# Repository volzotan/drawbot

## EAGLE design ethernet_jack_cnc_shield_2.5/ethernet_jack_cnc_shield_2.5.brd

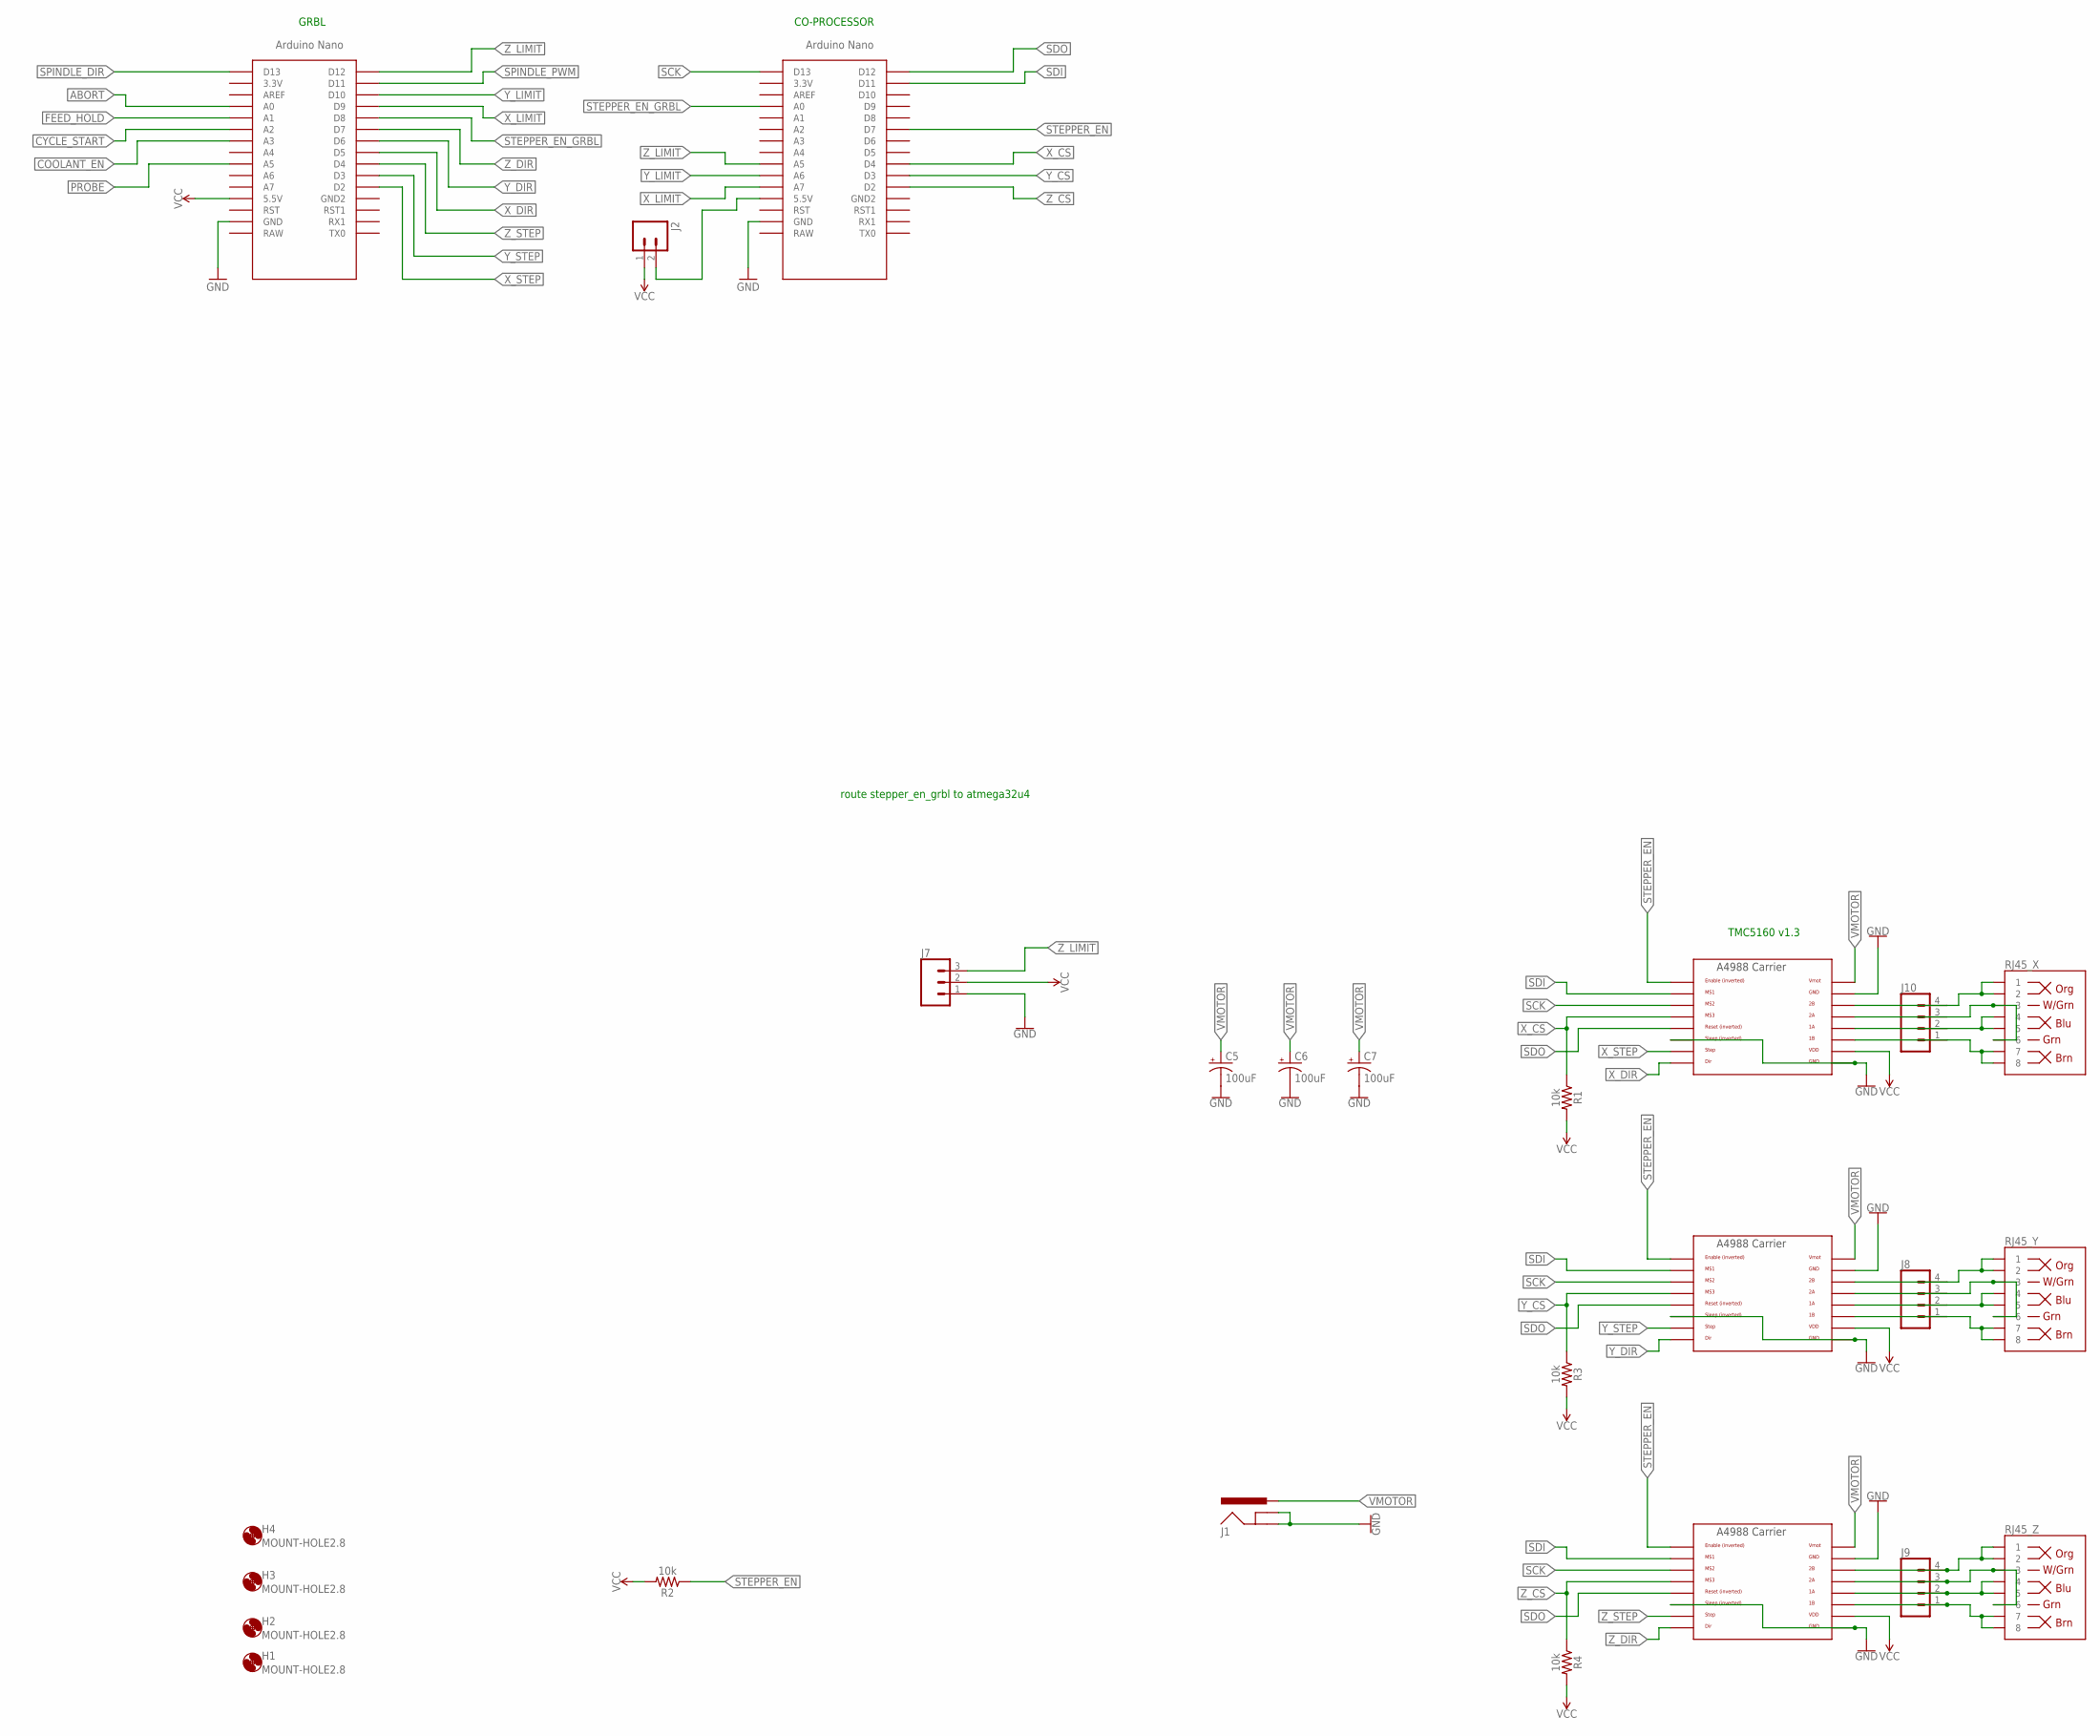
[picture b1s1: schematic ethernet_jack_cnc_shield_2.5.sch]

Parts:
C5, C6, C7: 100uF; PANASONIC_D
H1, H2, H3, H4: MOUNT-HOLE2.8; 2,8
J1: POWER_JACKPTH_BREAD; POWER_JACK_PTH_BREAD
J2: M02PTH; 1X02
J7: CONN_03; 1X03
J8, J9, J10: CONN_04; 1X04
R1, R2, R3, R4: 10k; 1206
RJ45_X, RJ45_Y, RJ45_Z: RJ45; RJ45-8
U$2, U$3, U$4: A4988BREAKOUT
U$5, U$7: NANO

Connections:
ABORT: U$5.A0
COOLANT_EN: U$5.A3
CYCLE_START: U$5.A2
FEED_HOLD: U$5.A1
GND: C5.-, C6.-, C7.-, J1.GND, J1.GNDBREAK, J7.1, U$2.GND, U$2.GND@0 (GND), U$2.SLP (SLEEP), U$3.GND, U$3.GND@0 (GND), U$3.SLP (SLEEP), U$4.GND, U$4.GND@0 (GND), U$4.SLP (SLEEP), U$5.GND, U$7.GND
unnamed: J10.4, RJ45_X.1, RJ45_X.2, U$4.2B
unnamed: J2.2, U$7.5V (5.5V)
unnamed: J10.3, RJ45_X.3, RJ45_X.6, U$4.2A
unnamed: J10.2, RJ45_X.4, RJ45_X.5, U$4.1A
unnamed: J10.1, RJ45_X.7, RJ45_X.8, U$4.1B
unnamed: J8.4, RJ45_Y.1, RJ45_Y.2, U$2.2B
unnamed: J8.3, RJ45_Y.3, RJ45_Y.6, U$2.2A
unnamed: J8.2, RJ45_Y.4, RJ45_Y.5, U$2.1A
unnamed: J8.1, RJ45_Y.7, RJ45_Y.8, U$2.1B
unnamed: J9.4, RJ45_Z.1, RJ45_Z.2, U$3.2B
unnamed: J9.3, RJ45_Z.3, RJ45_Z.6, U$3.2A
unnamed: J9.2, RJ45_Z.4, RJ45_Z.5, U$3.1A
unnamed: J9.1, RJ45_Z.7, RJ45_Z.8, U$3.1B
PROBE: U$5.A5
SCK: U$2.MS2, U$3.MS2, U$4.MS2, U$7.D13
SDI: U$2.MS1, U$3.MS1, U$4.MS1, U$7.D11
SDO: U$2.RST, U$3.RST, U$4.RST, U$7.D12
SPINDLE_DIR: U$5.D13
SPINDLE_PWM: U$5.D11
STEPPER_EN: R2.1, U$2.EN, U$3.EN, U$4.EN, U$7.D7
STEPPER_EN_GRBL: U$5.D8, U$7.A0
VCC: J2.1, J7.2, R1.2, R2.2, R3.2, R4.2, U$2.VDD, U$3.VDD, U$4.VDD, U$5.5V (5.5V)
VMOTOR: C5.+, C6.+, C7.+, J1.PWR, U$2.VMOT, U$3.VMOT, U$4.VMOT
X_CS: R1.1, U$4.MS3, U$7.D4
X_DIR: U$4.DIR, U$5.D5
X_LIMIT: U$5.D9, U$7.A7
X_STEP: U$4.STEP, U$5.D2
Y_CS: R3.1, U$2.MS3, U$7.D3
Y_DIR: U$2.DIR, U$5.D6
Y_LIMIT: U$5.D10, U$7.A6
Y_STEP: U$2.STEP, U$5.D3
Z_CS: R4.1, U$3.MS3, U$7.D2
Z_DIR: U$3.DIR, U$5.D7
Z_LIMIT: J7.3, U$5.D12, U$7.A5
Z_STEP: U$3.STEP, U$5.D4

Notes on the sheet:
route stepper_en_grbl to atmega32u4
GRBL
CO-PROCESSOR
TMC5160 v1.3

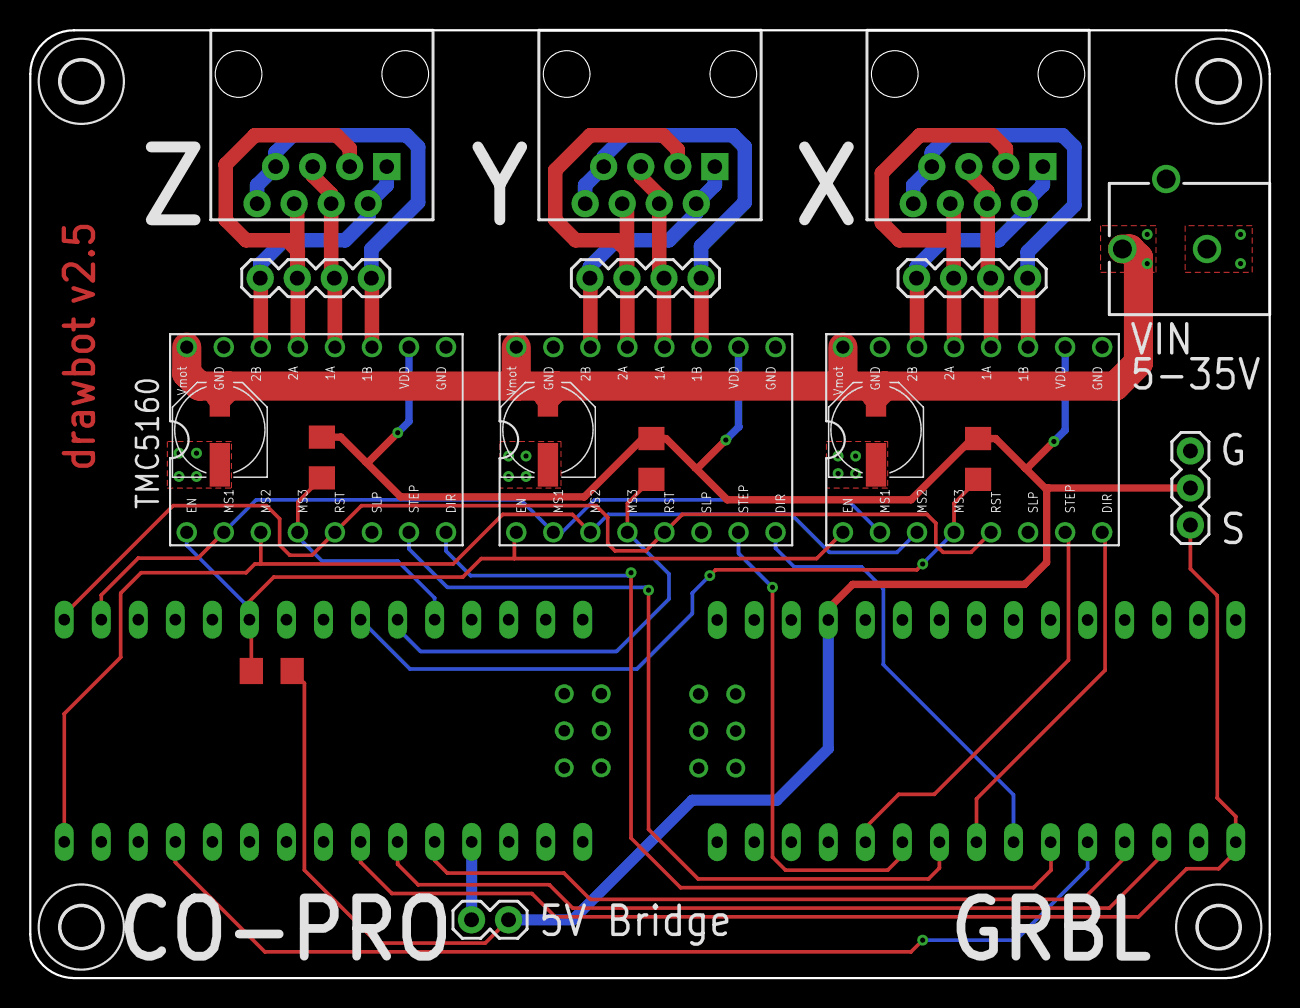
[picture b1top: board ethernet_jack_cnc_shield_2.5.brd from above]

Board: 2 copper layers, 85.0 x 65.0 mm, 25 parts (0 on the bottom side), 33 nets.

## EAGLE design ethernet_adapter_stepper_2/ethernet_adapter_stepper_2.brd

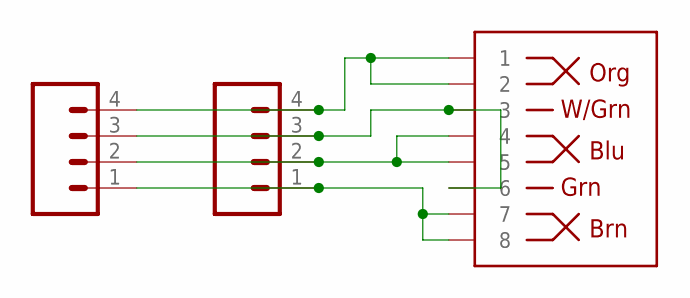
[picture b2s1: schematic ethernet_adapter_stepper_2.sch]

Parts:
J1: RJ45; RJ45-8
J2: CONN_04; 1X04
J4: CONN_04SCREW; SCREWTERMINAL-3.5MM-4

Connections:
unnamed: J1.1, J1.2, J2.4, J4.4
unnamed: J1.4, J1.5, J2.2, J4.2
unnamed: J1.3, J1.6, J2.3, J4.3
unnamed: J1.7, J1.8, J2.1, J4.1

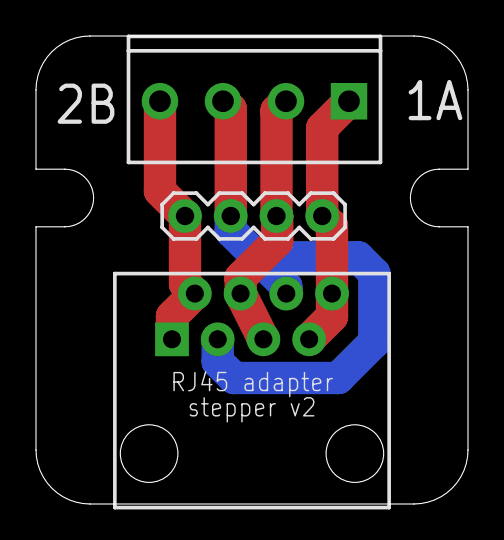
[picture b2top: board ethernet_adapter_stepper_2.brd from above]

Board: 2 copper layers, 24.0 x 26.0 mm, 3 parts (0 on the bottom side), 4 nets.

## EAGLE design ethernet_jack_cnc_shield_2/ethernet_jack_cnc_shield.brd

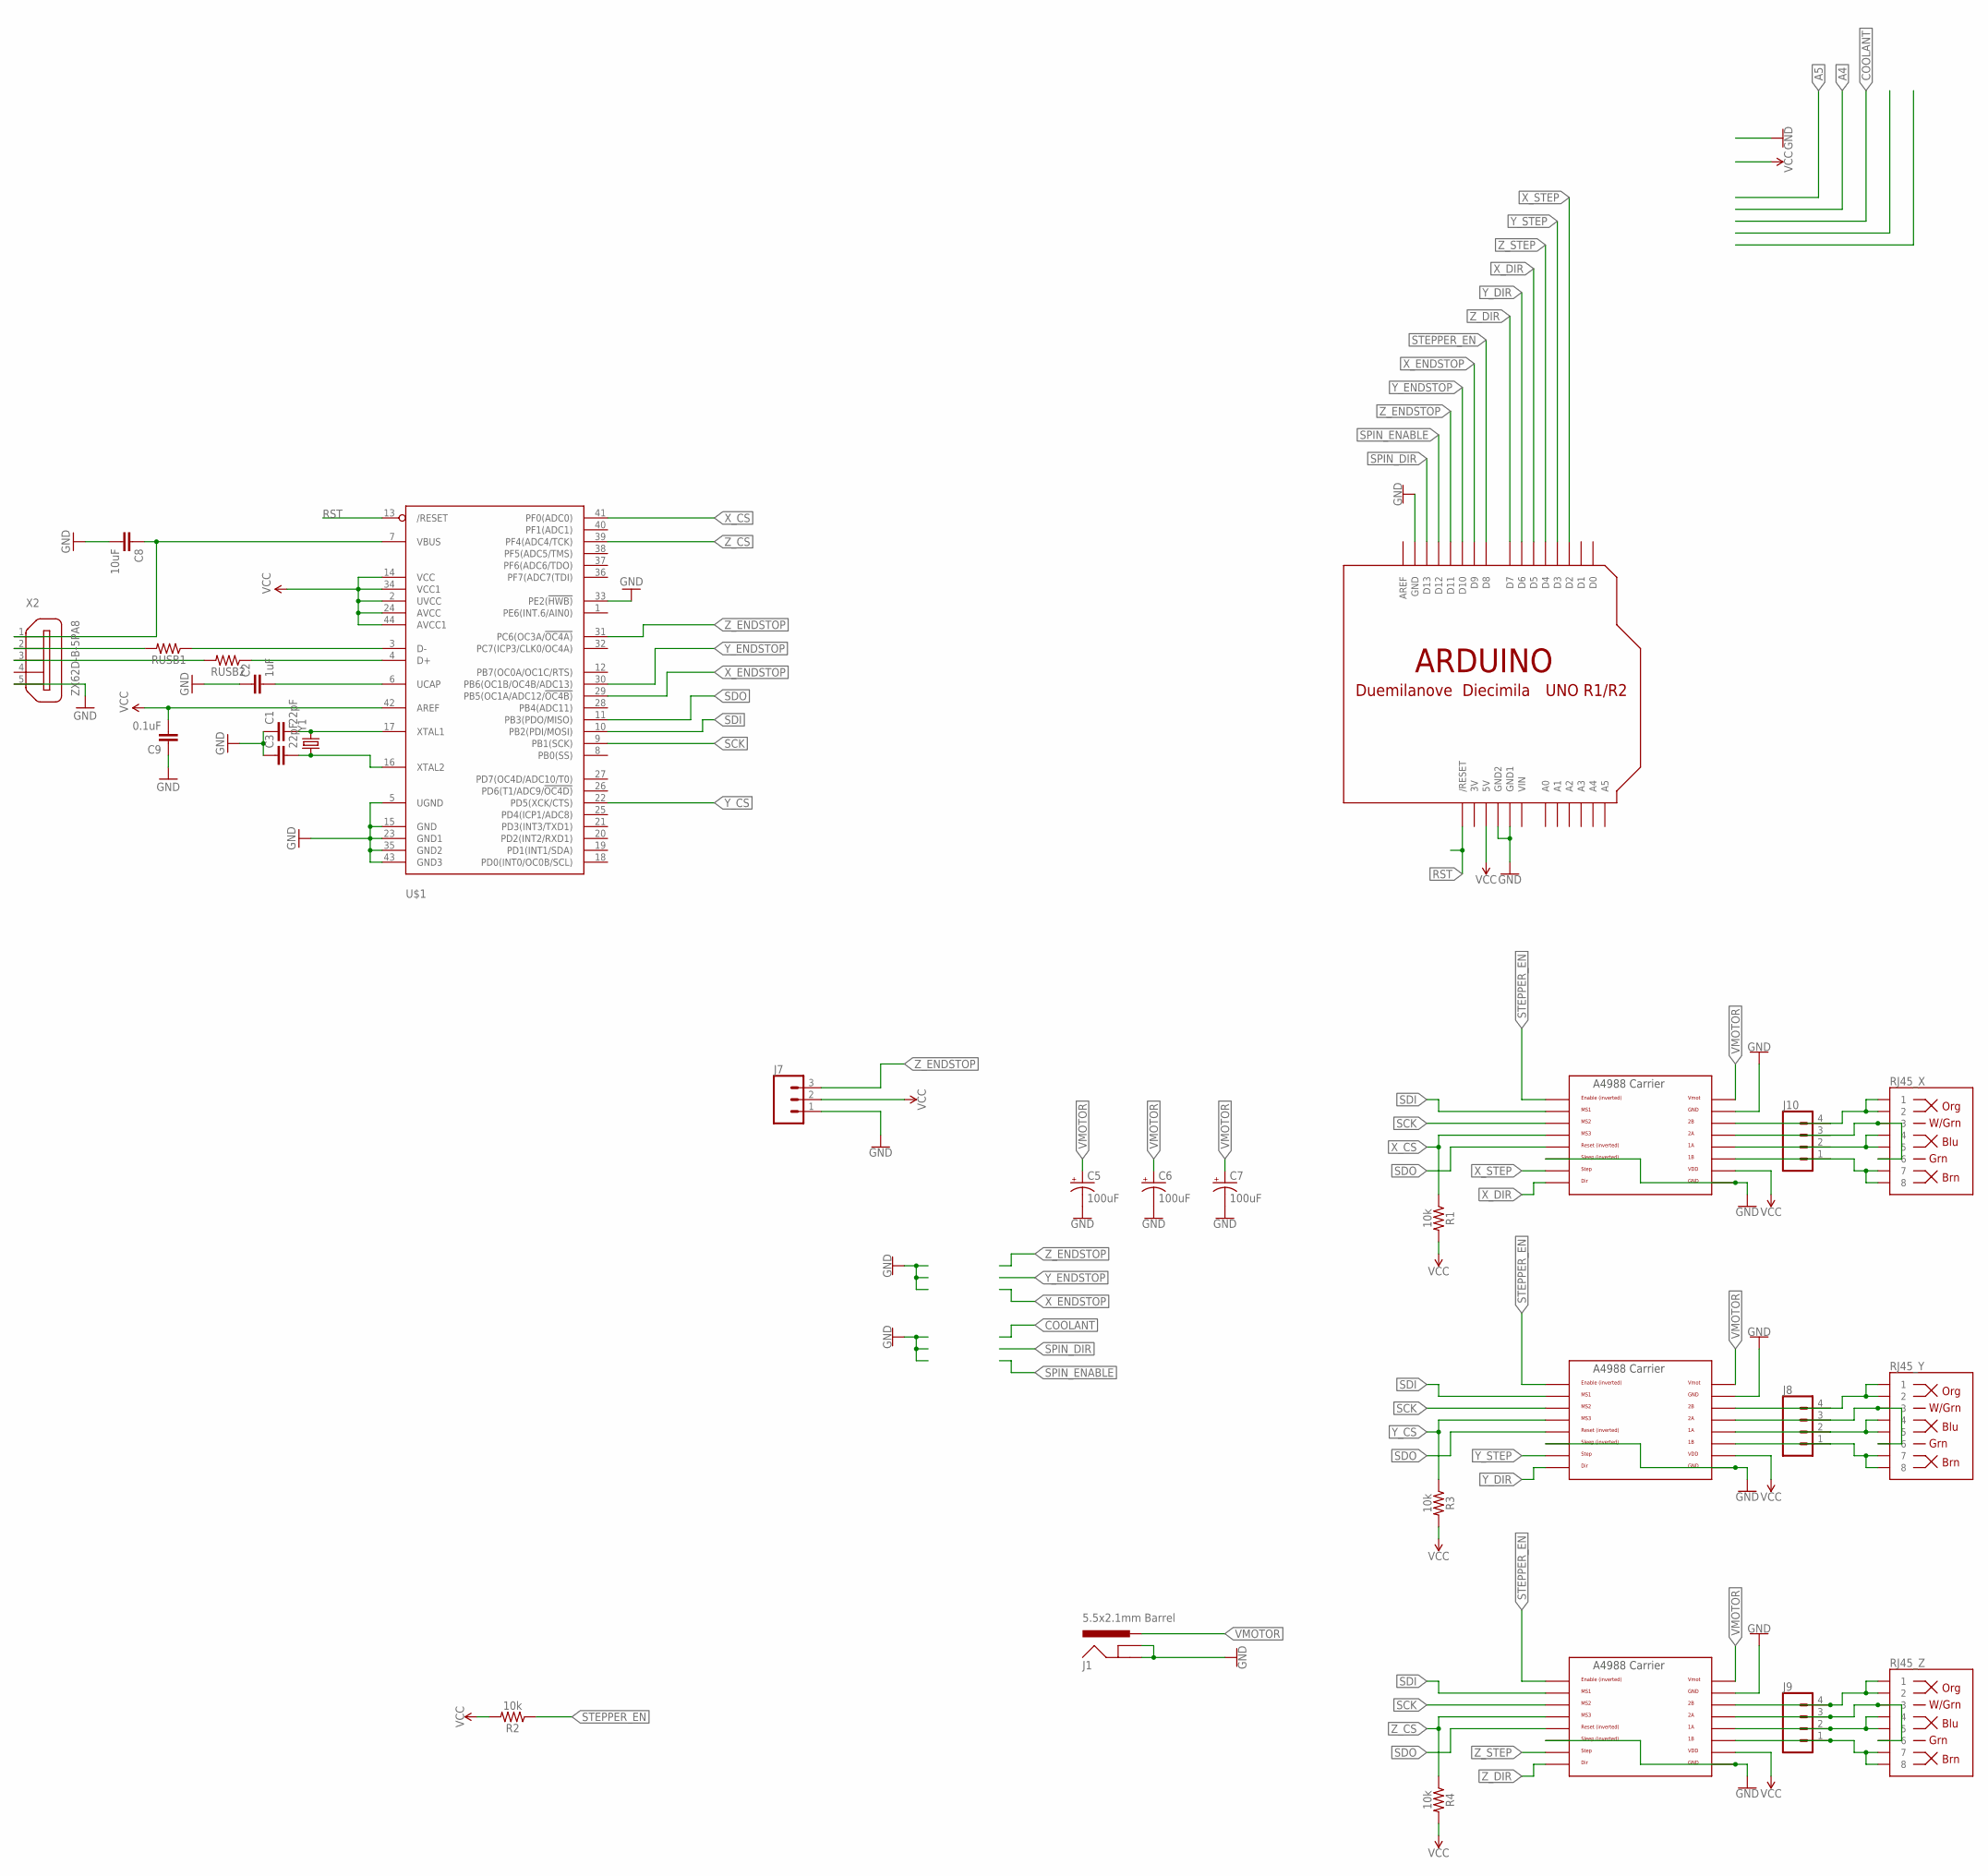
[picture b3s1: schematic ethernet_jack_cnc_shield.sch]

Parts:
C1, C3: 22pF; 1206
C2: 1uF; 1206
C5, C6, C7: 100uF; PANASONIC_D
C8: 10uF; 1206
C9: 0.1uF; 1206
J1: 5.5x2.1mm Barrel; POWER_JACK_SMD
J7: CONN_03; 1X03
J8, J9, J10: CONN_04; 1X04
R1, R2, R3, R4: 10k; 1206
RJ45_X, RJ45_Y, RJ45_Z: RJ45; RJ45-8
RUSB1, RUSB2: RESISTOR1206; 1206
U$1: ATMEGA32U4-AU; TQFP44
U$2, U$3, U$4: A4988BREAKOUT
U$6: ARDUINOUNO; ARDUINO
X2: ZX62D-B-5PA8
Y1: CRYSTALCRYSTAL-SMD-5X3-16MHZ; CRYSTAL-SMD-5X3

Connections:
3V: U$6.3V
GND: C1.1, C2.1, C3.1, C5.-, C6.-, C7.-, C8.2, C9.1, J1.GND (GNDBREAK), J1.P$4 (GND), J7.1, U$1.5 (UGND), U$1.15 (GND), U$1.23 (GND1), U$1.33 (PE2(!HWB)), U$1.35 (GND2), U$1.43 (GND3), U$2.GND, U$2.GND@0 (GND), U$2.SLP (SLEEP), U$3.GND, U$3.GND@0 (GND), U$3.SLP (SLEEP), U$4.GND, U$4.GND@0 (GND), U$4.SLP (SLEEP), U$6.GND, U$6.GND1, U$6.GND2, X2.5
unnamed: J10.4, RJ45_X.1, RJ45_X.2, U$4.2B
unnamed: RUSB1.1, U$1.3 (D-)
unnamed: J10.3, RJ45_X.3, RJ45_X.6, U$4.2A
unnamed: RUSB2.1, U$1.4 (D+)
unnamed: J10.2, RJ45_X.4, RJ45_X.5, U$4.1A
unnamed: C2.2, U$1.6 (UCAP)
unnamed: J10.1, RJ45_X.7, RJ45_X.8, U$4.1B
unnamed: C1.2, U$1.17 (XTAL1), Y1.3 (2)
unnamed: C3.2, U$1.16 (XTAL2), Y1.1
unnamed: RUSB1.2, X2.2
unnamed: RUSB2.2, X2.3
unnamed: J8.4, RJ45_Y.1, RJ45_Y.2, U$2.2B
unnamed: J8.3, RJ45_Y.3, RJ45_Y.6, U$2.2A
unnamed: J8.2, RJ45_Y.4, RJ45_Y.5, U$2.1A
unnamed: J8.1, RJ45_Y.7, RJ45_Y.8, U$2.1B
unnamed: J9.4, RJ45_Z.1, RJ45_Z.2, U$3.2B
unnamed: J9.3, RJ45_Z.3, RJ45_Z.6, U$3.2A
unnamed: J9.2, RJ45_Z.4, RJ45_Z.5, U$3.1A
unnamed: J9.1, RJ45_Z.7, RJ45_Z.8, U$3.1B
RST: U$1.13 (/RESET), U$6.RESET (/RESET)
SCK: U$1.9 (PB1(SCK)), U$2.MS2, U$3.MS2, U$4.MS2
SDI: U$1.10 (PB2(PDI/MOSI)), U$2.MS1, U$3.MS1, U$4.MS1
SDO: U$1.11 (PB3(PDO/MISO)), U$2.RST, U$3.RST, U$4.RST
SPIN_DIR: U$6.D13
SPIN_ENABLE: U$6.D12
STEPPER_EN: R2.1, U$2.EN, U$3.EN, U$4.EN, U$6.D8
VBUS: C8.1, U$1.7 (VBUS), X2.1
VCC: C9.2, J7.2, R1.2, R2.2, R3.2, R4.2, U$1.2 (UVCC), U$1.14 (VCC), U$1.24 (AVCC), U$1.34 (VCC1), U$1.42 (AREF), U$1.44 (AVCC1), U$2.VDD, U$3.VDD, U$4.VDD, U$6.5V
VIN: U$6.VIN
VMOTOR: C5.+, C6.+, C7.+, J1.VIN0 (PWR), U$2.VMOT, U$3.VMOT, U$4.VMOT
X_CS: R1.1, U$1.41 (PF0(ADC0)), U$4.MS3
X_DIR: U$4.DIR, U$6.D5
X_ENDSTOP: U$1.29 (PB5(OC1A/ADC12/!OC4B)), U$6.D9
X_STEP: U$4.STEP, U$6.D2
Y_CS: R3.1, U$1.22 (PD5(XCK/CTS)), U$2.MS3
Y_DIR: U$2.DIR, U$6.D6
Y_ENDSTOP: U$1.30 (PB6(OC1B/OC4B/ADC13)), U$6.D10
Y_STEP: U$2.STEP, U$6.D3
Z_CS: R4.1, U$1.39 (PF4(ADC4/TCK)), U$3.MS3
Z_DIR: U$3.DIR, U$6.D7
Z_ENDSTOP: J7.3, U$1.31 (PC6(OC3A/!OC4A)), U$6.D11
Z_STEP: U$3.STEP, U$6.D4

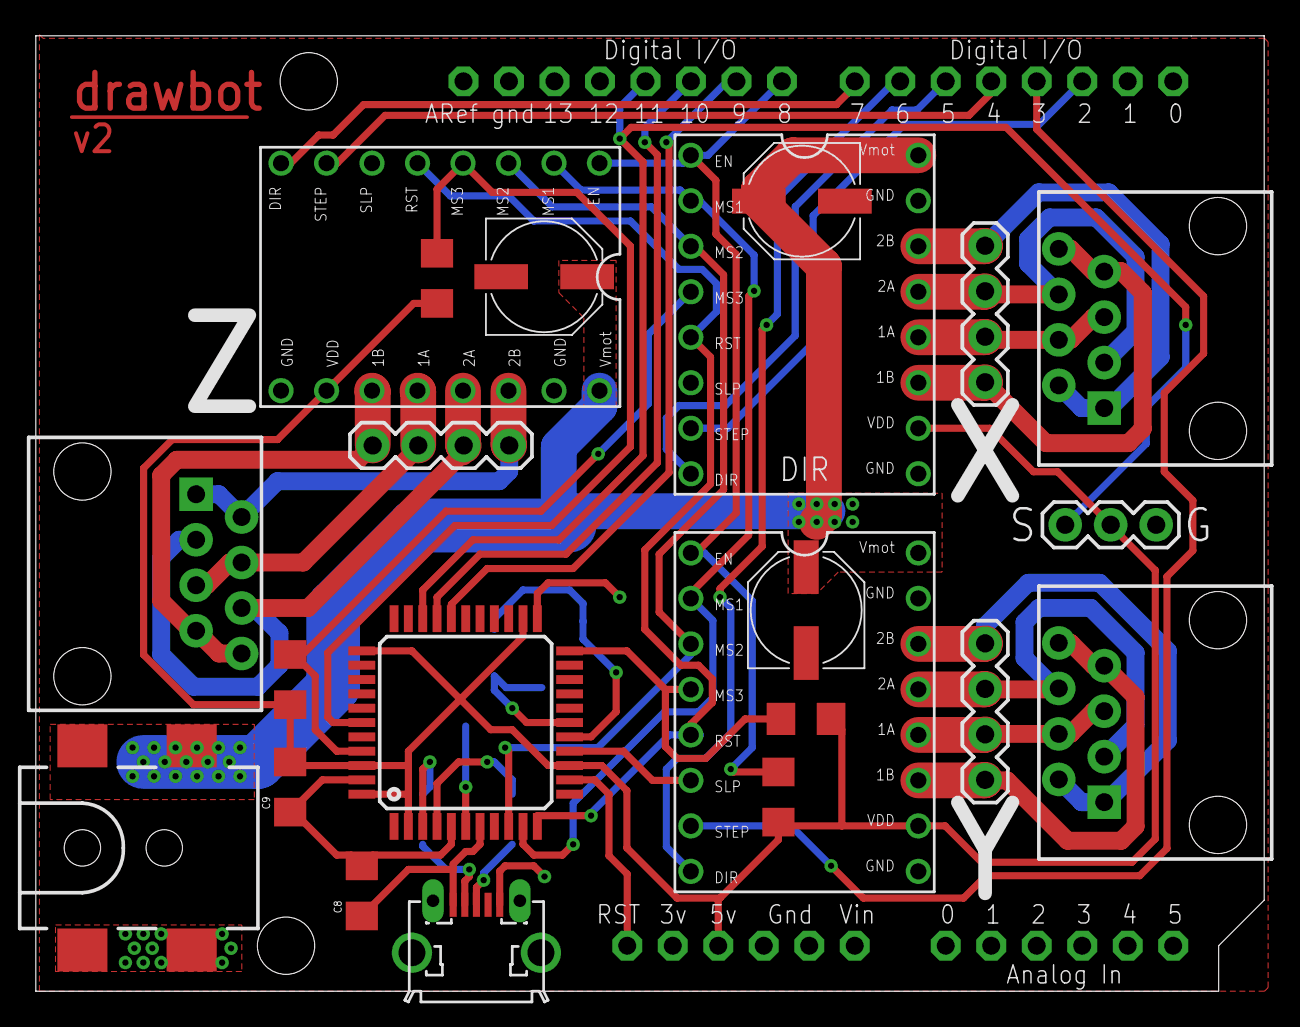
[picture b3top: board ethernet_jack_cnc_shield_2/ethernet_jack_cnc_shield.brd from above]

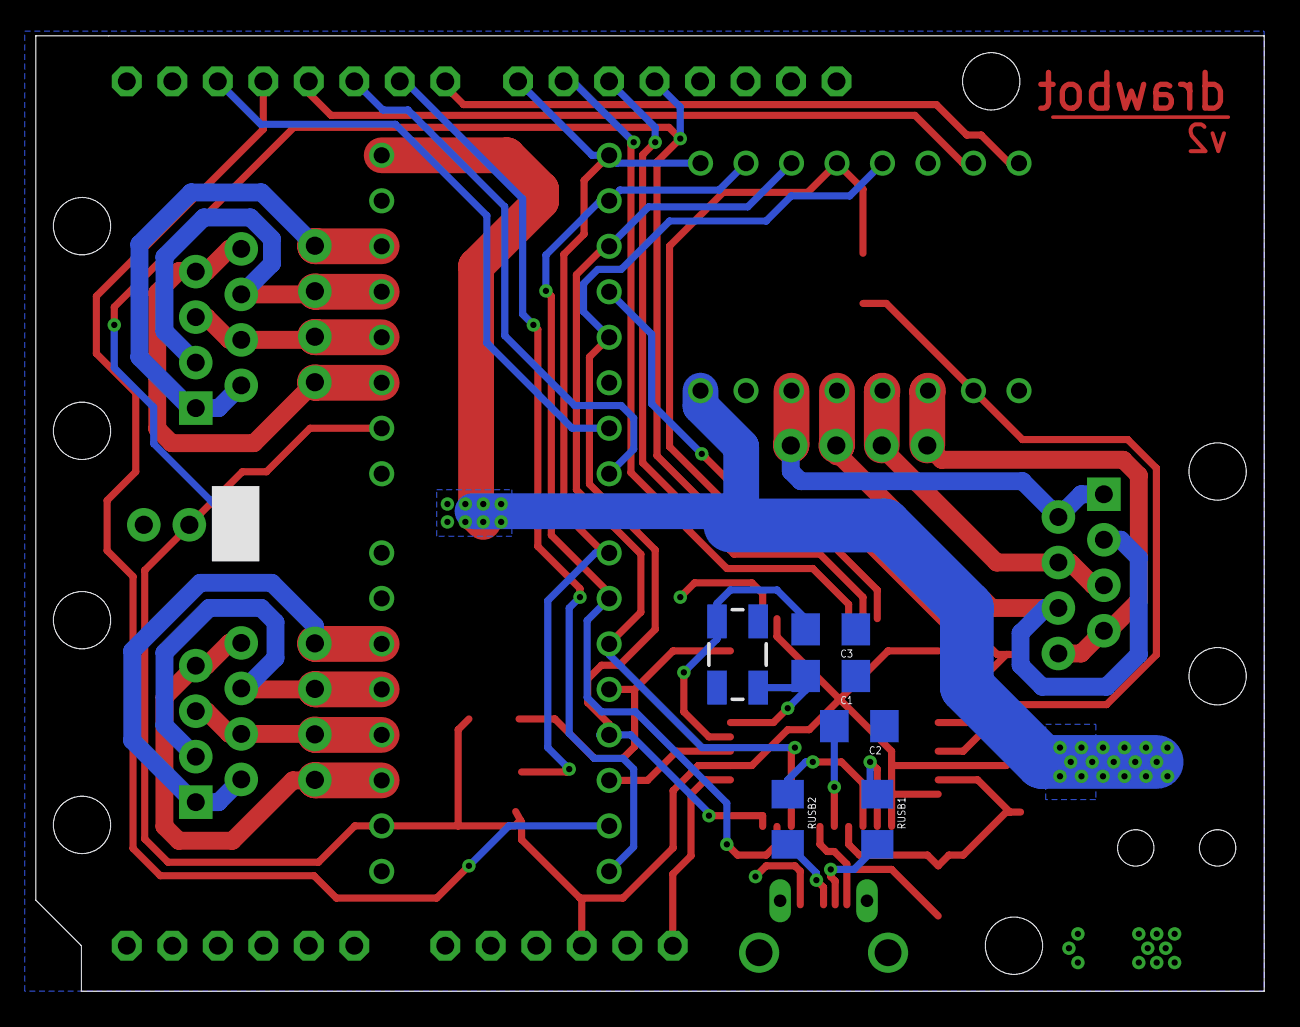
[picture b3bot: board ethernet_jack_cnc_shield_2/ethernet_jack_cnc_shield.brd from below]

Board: 2 copper layers, 68.6 x 53.3 mm, 29 parts (6 on the bottom side), 40 nets.

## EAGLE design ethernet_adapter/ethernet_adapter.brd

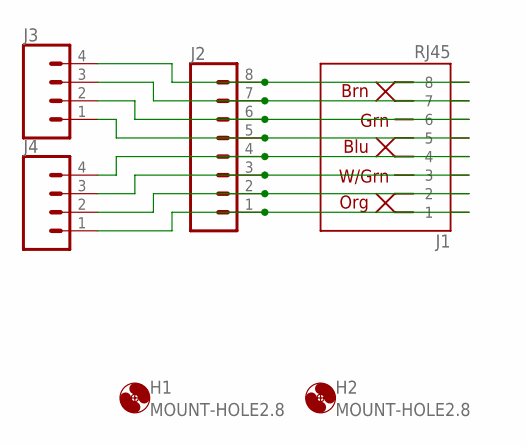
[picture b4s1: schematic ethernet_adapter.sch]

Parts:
H1, H2: MOUNT-HOLE2.8; 2,8
J1: RJ45; RJ45-8
J2: CONN_08LONGPADS; 1X08_LONGPADS
J3, J4: CONN_04SCREW; SCREWTERMINAL-3.5MM-4

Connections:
unnamed: J1.8, J2.8, J3.4
unnamed: J1.7, J2.7, J3.3
unnamed: J1.6, J2.6, J3.2
unnamed: J1.5, J2.5, J3.1
unnamed: J1.4, J2.4, J4.4
unnamed: J1.3, J2.3, J4.3
unnamed: J1.2, J2.2, J4.2
unnamed: J1.1, J2.1, J4.1

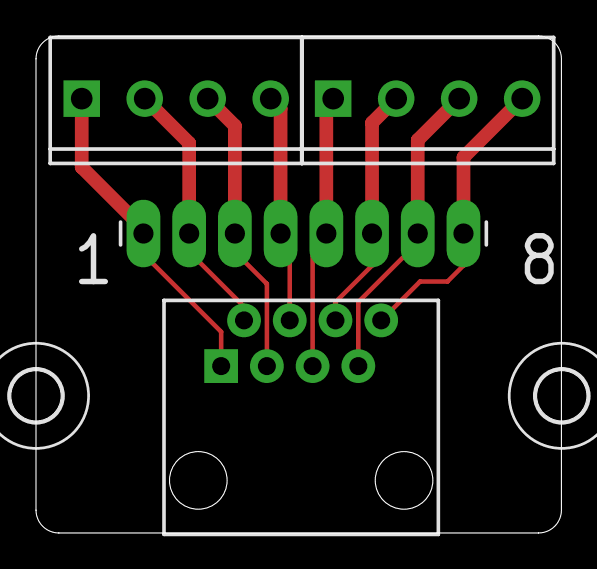
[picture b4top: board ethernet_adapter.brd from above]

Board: 2 copper layers, 29.2 x 27.6 mm, 6 parts (0 on the bottom side), 8 nets.

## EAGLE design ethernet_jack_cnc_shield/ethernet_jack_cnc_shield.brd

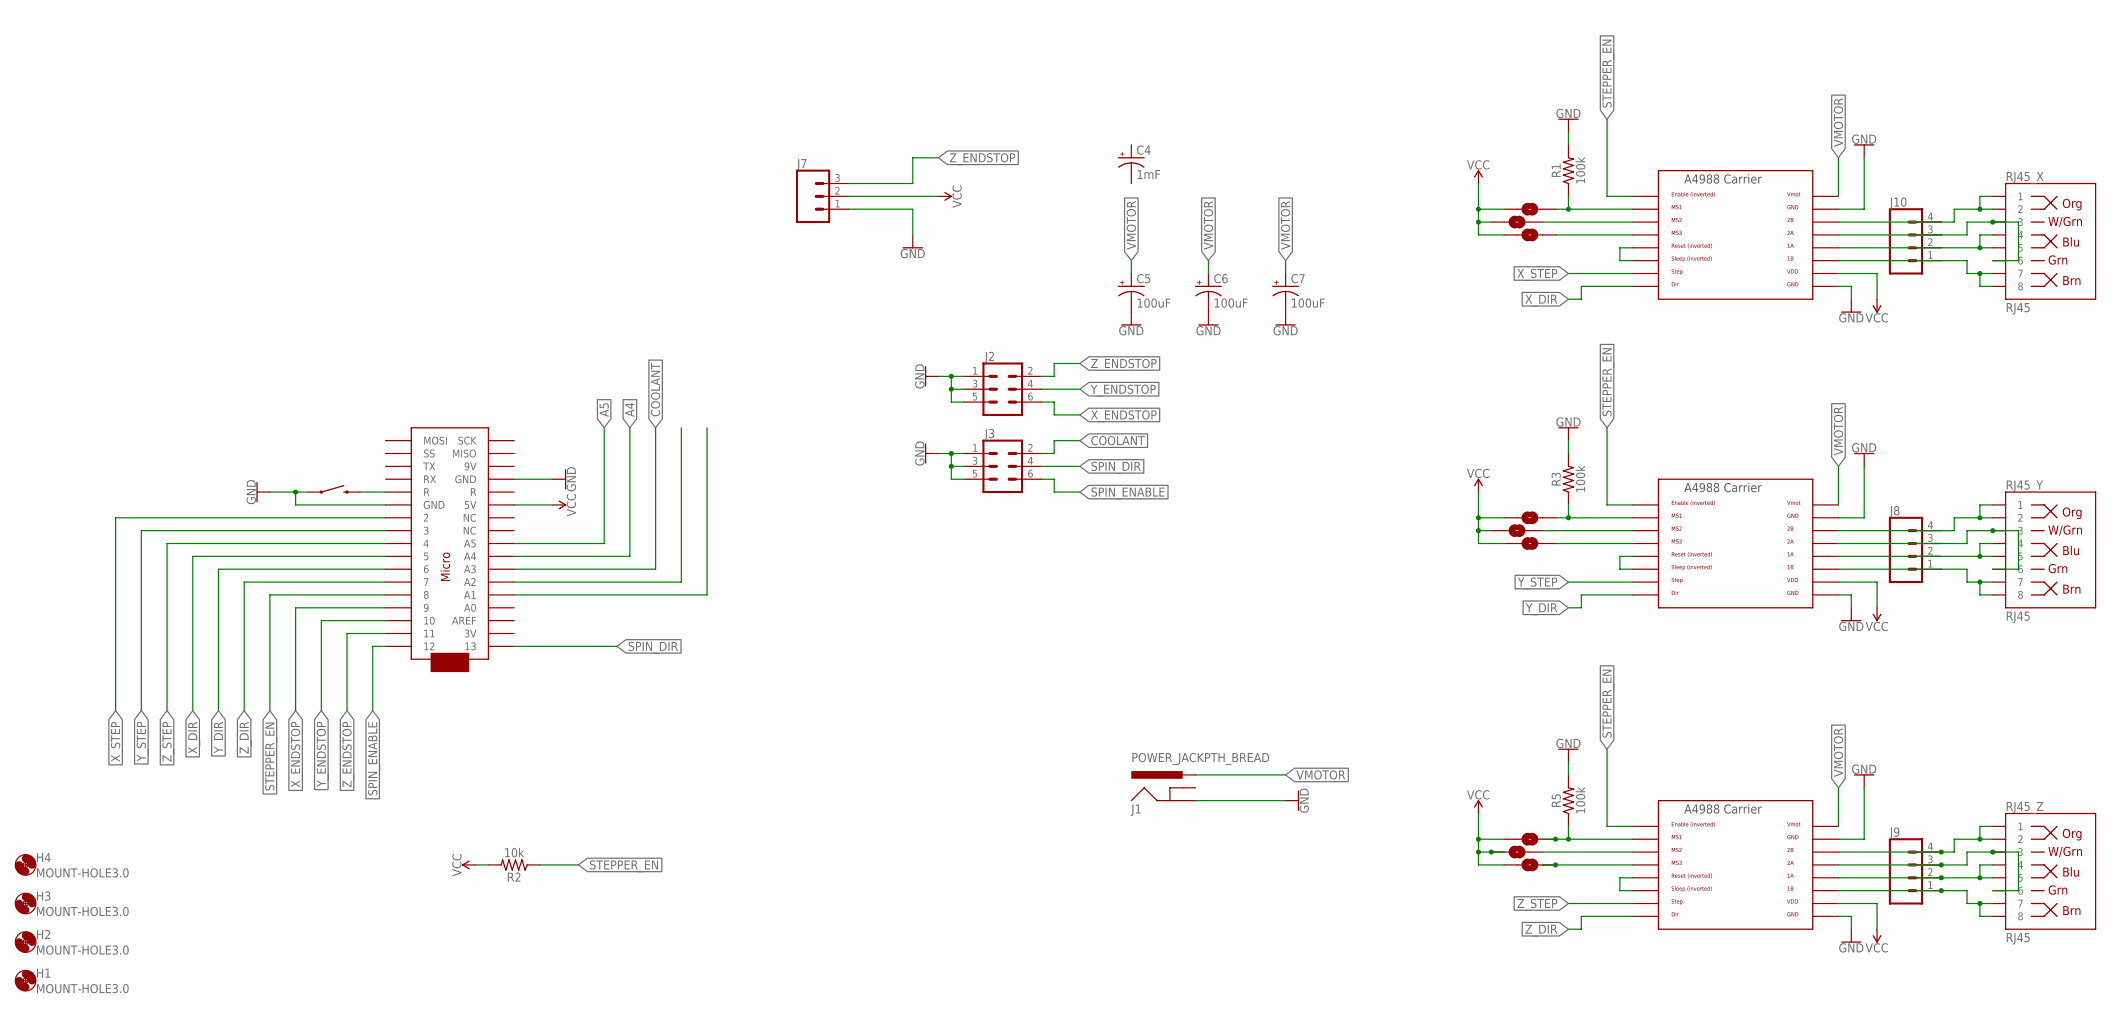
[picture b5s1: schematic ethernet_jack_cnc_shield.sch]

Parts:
C4: 1mF; CPOL-RADIAL-5MM-10MM
C5, C6, C7: 100uF; CPOL-RADIAL-2.5MM-6.5MM
H1, H2, H3, H4: MOUNT-HOLE3.0; 3,0
J1: POWER_JACKPTH_BREAD; POWER_JACK_PTH_BREAD
J2, J3: CONN_03X2NO_SILK; 2X3-NS
J7: CONN_03; 1X03
J8, J9, J10: CONN_04; 1X04
JP1, JP2, JP3, JP4, JP5, JP6, JP7, JP8, JP9: JUMPER-SMT_2_NO_SILK_ROUND; SMT-JUMPER_2_NO_SILK_ROUND
R1, R3, R5: 100k; 1206
R2: 10k; 1206
RJ45_X, RJ45_Y, RJ45_Z: RJ45; RJ45-8
S1: MOMENTARY-SWITCH-SPST-PTH-RIGHT-ANGLE-KIT; TACTILE_SWITCH_PTH_RIGHT_ANGLE_KIT
U$1: ARDUINOMICRO
U$2, U$3, U$4: A4988BREAKOUT

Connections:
A4: U$1.P$27 (A4)
A5: U$1.P$26 (A5)
COOLANT: J3.2, U$1.P$28 (A3)
GND: C5.2 (-), C6.2 (-), C7.2 (-), J1.GND, J2.1, J2.3, J2.5, J3.1, J3.3, J3.5, J7.1, R1.2, R3.2, R5.2, S1.1, U$1.P$12 (GND), U$1.P$21 (GND), U$2.GND, U$2.GND@0 (GND), U$3.GND, U$3.GND@0 (GND), U$4.GND, U$4.GND@0 (GND)
unnamed: J10.4, RJ45_X.1, RJ45_X.2, U$4.2B
unnamed: J10.3, RJ45_X.3, RJ45_X.6, U$4.2A
unnamed: J10.2, RJ45_X.4, RJ45_X.5, U$4.1A
unnamed: J10.1, RJ45_X.7, RJ45_X.8, U$4.1B
unnamed: S1.2, U$1.P$22 (R)
unnamed: JP6.2, U$4.MS3
unnamed: U$4.RST, U$4.SLP (SLEEP)
unnamed: JP4.2, R1.1, U$4.MS1
unnamed: JP5.2, U$4.MS2
unnamed: J8.4, RJ45_Y.1, RJ45_Y.2, U$2.2B
unnamed: J8.3, RJ45_Y.3, RJ45_Y.6, U$2.2A
unnamed: J8.2, RJ45_Y.4, RJ45_Y.5, U$2.1A
unnamed: J8.1, RJ45_Y.7, RJ45_Y.8, U$2.1B
unnamed: JP7.2, U$2.MS3
unnamed: JP1.2, R3.1, U$2.MS1
unnamed: JP2.2, U$2.MS2
unnamed: U$2.RST, U$2.SLP (SLEEP)
unnamed: J9.4, RJ45_Z.1, RJ45_Z.2, U$3.2B
unnamed: J9.3, RJ45_Z.3, RJ45_Z.6, U$3.2A
unnamed: J9.2, RJ45_Z.4, RJ45_Z.5, U$3.1A
unnamed: J9.1, RJ45_Z.7, RJ45_Z.8, U$3.1B
unnamed: JP9.2, U$3.MS3
unnamed: JP3.2, R5.1, U$3.MS1
unnamed: JP8.2, U$3.MS2
unnamed: U$3.RST, U$3.SLP (SLEEP)
SPIN_DIR: J3.4, U$1.P$34 (13)
SPIN_ENABLE: J3.6, U$1.P$1 (12)
STEPPER_EN: R2.1, U$1.P$5 (8), U$2.EN, U$3.EN, U$4.EN
VCC: J7.2, JP1.1, JP2.1, JP3.1, JP4.1, JP5.1, JP6.1, JP7.1, JP8.1, JP9.1, R2.2, U$1.P$23 (5V), U$2.VDD, U$3.VDD, U$4.VDD
VMOTOR: C5.1 (+), C6.1 (+), C7.1 (+), J1.PWR, U$2.VMOT, U$3.VMOT, U$4.VMOT
X_DIR: U$1.P$8 (5), U$4.DIR
X_ENDSTOP: J2.6, U$1.P$4 (9)
X_STEP: U$1.P$11 (2), U$4.STEP
Y_DIR: U$1.P$7 (6), U$2.DIR
Y_ENDSTOP: J2.4, U$1.P$3 (10)
Y_STEP: U$1.P$10 (3), U$2.STEP
Z_DIR: U$1.P$6 (7), U$3.DIR
Z_ENDSTOP: J2.2, J7.3, U$1.P$2 (11)
Z_STEP: U$1.P$9 (4), U$3.STEP

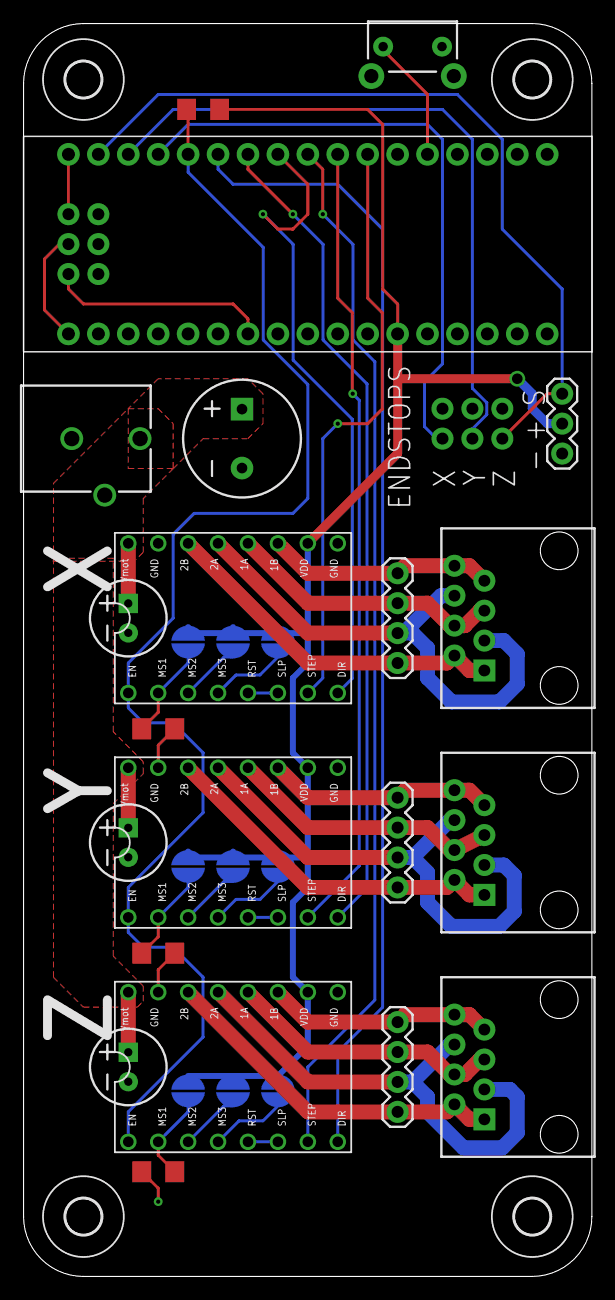
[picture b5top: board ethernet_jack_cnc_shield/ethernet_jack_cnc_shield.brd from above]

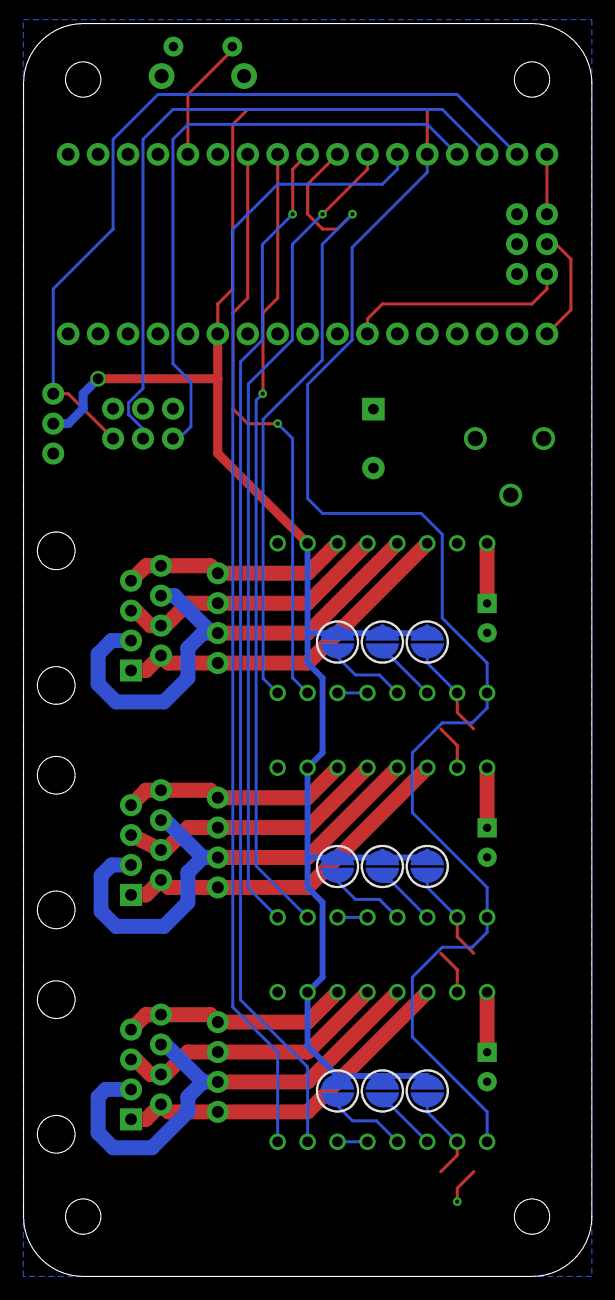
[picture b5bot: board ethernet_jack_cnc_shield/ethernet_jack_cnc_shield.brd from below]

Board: 2 copper layers, 48.2 x 106.3 mm, 36 parts (9 on the bottom side), 41 nets.

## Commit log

2019-05-14 Marlin Configuration
2019-06-03 grbl servo version for beamplot (changes based on buildlogs repo)
2019-06-03 grbl_mega
2019-06-03 no more marlin
2019-06-03 grbl settings
2019-09-14 eagle files for ethernet CNC boards and adapters
2019-10-31 ethernet adapter 2 and ethernet shield 2
2020-06-01 New drawbot v2.5 PCB
2020-06-01 updated gitignore to ignore eagle temp files
2020-12-01 firmwares
2020-12-01 README
2021-01-20 squareplot STEP file
2026-03-19 added squareplot Fusion360 file and missing components in the STEP file

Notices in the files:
parts and their libraries:
SparkFun-Connectors: Licensing: Creative Commons ShareAlike 4.0 International - https://creativecommons.org/licenses/by-sa/4.0
